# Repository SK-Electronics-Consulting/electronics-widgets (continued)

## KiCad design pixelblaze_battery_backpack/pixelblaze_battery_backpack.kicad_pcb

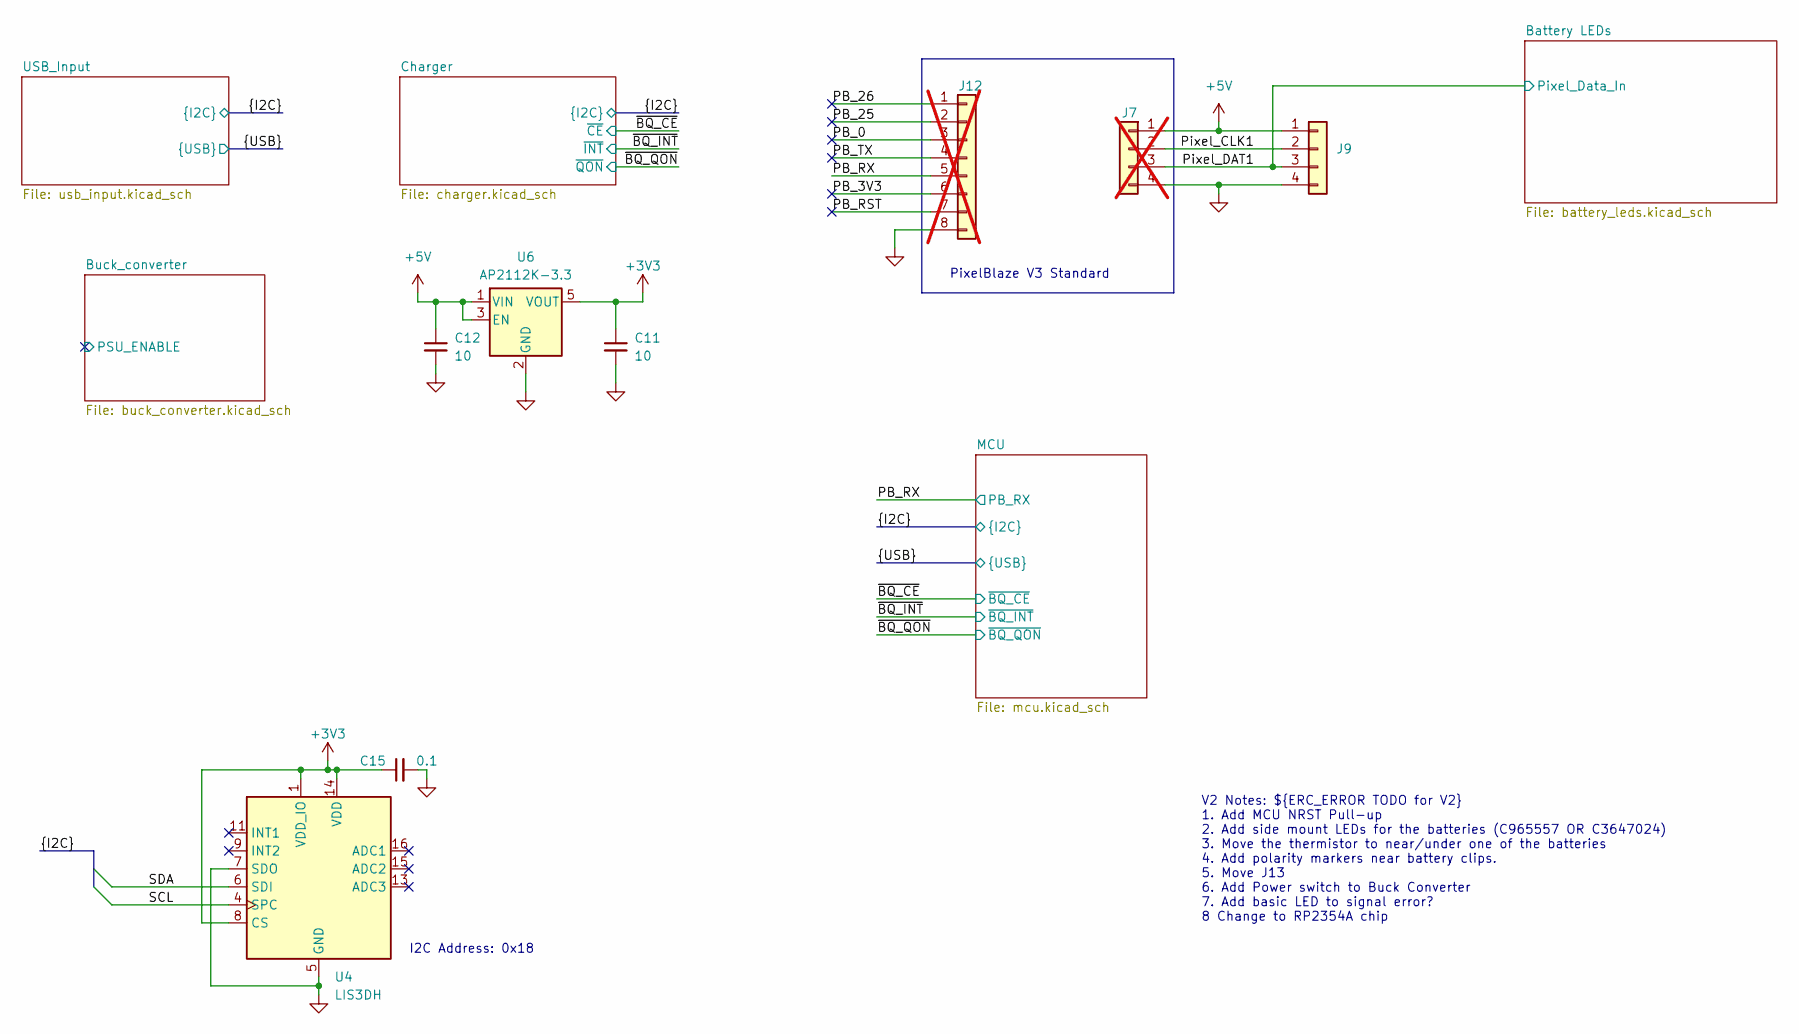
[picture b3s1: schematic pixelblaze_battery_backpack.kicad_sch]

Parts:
C11, C12: 10; C_0603_1608Metric; MPN GRM188R6YA106MA73D; JLCPCB Part No. C194427
C15: 0.1; C_0402_1005Metric; MPN GRM155R62A104KE14D; JLCPCB Part No. C162178
J7: Conn_01x04; PinHeader_1x04_P2.54mm_Vertical; not fitted
J9: Conn_01x04; Molex_Micro-Fit_3.0_43650-0415_1x04_P3.00mm_Vertical; MPN 436500415; JLCPCB Part No. C293547
J12: Conn_01x08; PinHeader_1x08_P2.54mm_Vertical; not fitted
U4: LIS3DH; LGA-16_3x3mm_P0.5mm_LayoutBorder3x5y; MPN LIS3DHTR; JLCPCB Part No. C15134
U6: AP2112K-3.3; SOT-23-5; MPN AP2112K-3.3TRG1; JLCPCB Part No. C51118

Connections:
+3V3: C11.1, C15.1, U4.1 (VDD_IO), U4.8 (CS), U4.14 (VDD), U6.5 (VOUT); also elsewhere on the board
+5V: C12.1, J7.1, J9.1, U6.1 (VIN), U6.3 (EN); also elsewhere on the board
/PB_0: J12.3
/PB_3V3: J12.6
/PB_25: J12.2
/PB_26: J12.1
/PB_RST: J12.7
/PB_RX: J12.5; also elsewhere on the board
/PB_TX: J12.4
/Pixel_CLK1: J7.2, J9.2
/Pixel_DAT1: J7.3, J9.3; also elsewhere on the board
/SCL: U4.4 (SPC); also elsewhere on the board
/SDA: U4.6 (SDI); also elsewhere on the board
GND: C11.2, C12.2, C15.2, J7.4, J9.4, J12.8, U4.5 (GND), U4.7 (SDO), U4.10 (GND), U4.12 (GND), U6.2 (GND); also elsewhere on the board

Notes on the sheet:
V2 Notes: ${ERC_ERROR TODO for V2} 1. Add MCU NRST Pull-up 2. Add side mount LEDs for the batteries (C965557 OR C3647024) 3. Move the thermistor to near/under one of the batteries 4. Add polarity markers near battery clips. 5. Move J13 6. Add Power switch to Buck Converter 7. Add basic LED to signa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
I2C Address: 0x18
PixelBlaze V3 Standard

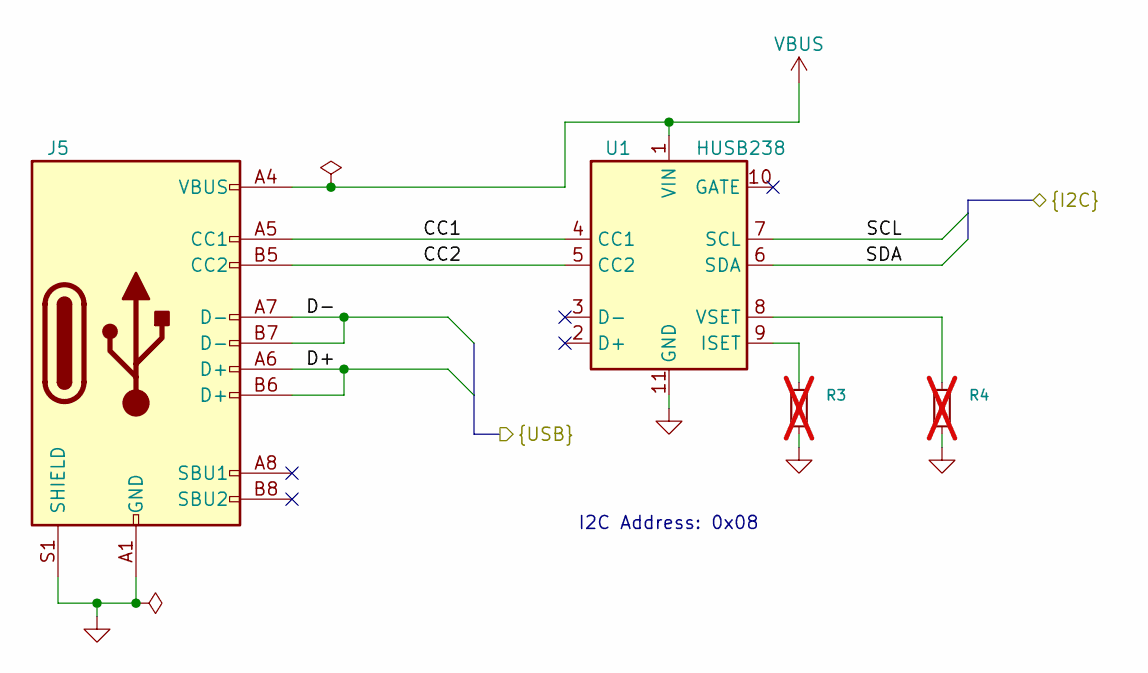
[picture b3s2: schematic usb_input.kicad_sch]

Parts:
J5: USB_C_Receptacle_USB2.0_16P; USB_C_Receptacle_HRO_TYPE-C-31-M-12; MPN TYPE-C-31-M-12; JLCPCB Part No. C165948
R3, R4: R_Small; R_0402_1005Metric; not fitted
U1: HUSB238; WDFN-10-1EP_3x3mm_P0.5mm_EP1.8x2.5mm; MPN HUSB238_002DD; JLCPCB Part No. C7471904

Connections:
/D+: J5.A6 (D+), J5.B6 (D+); also elsewhere on the board
/D-: J5.A7 (D-), J5.B7 (D-); also elsewhere on the board
/SCL: U1.7 (SCL); also elsewhere on the board
/SDA: U1.6 (SDA); also elsewhere on the board
/USB_Input/CC1: J5.A5 (CC1), U1.4 (CC1)
/USB_Input/CC2: J5.B5 (CC2), U1.5 (CC2)
GND: J5.A1 (GND), J5.A12 (GND), J5.B1 (GND), J5.B12 (GND), J5.S1 (SHIELD), J5.SH (SHIELD), R3.2, R4.2, U1.11 (GND); also elsewhere on the board
unnamed: R3.1, U1.9 (ISET)
unnamed: R4.1, U1.8 (VSET)
VBUS: J5.A4 (VBUS), J5.A9 (VBUS), J5.B4 (VBUS), J5.B9 (VBUS), U1.1 (VIN); also elsewhere on the board

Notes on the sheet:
I2C Address: 0x08

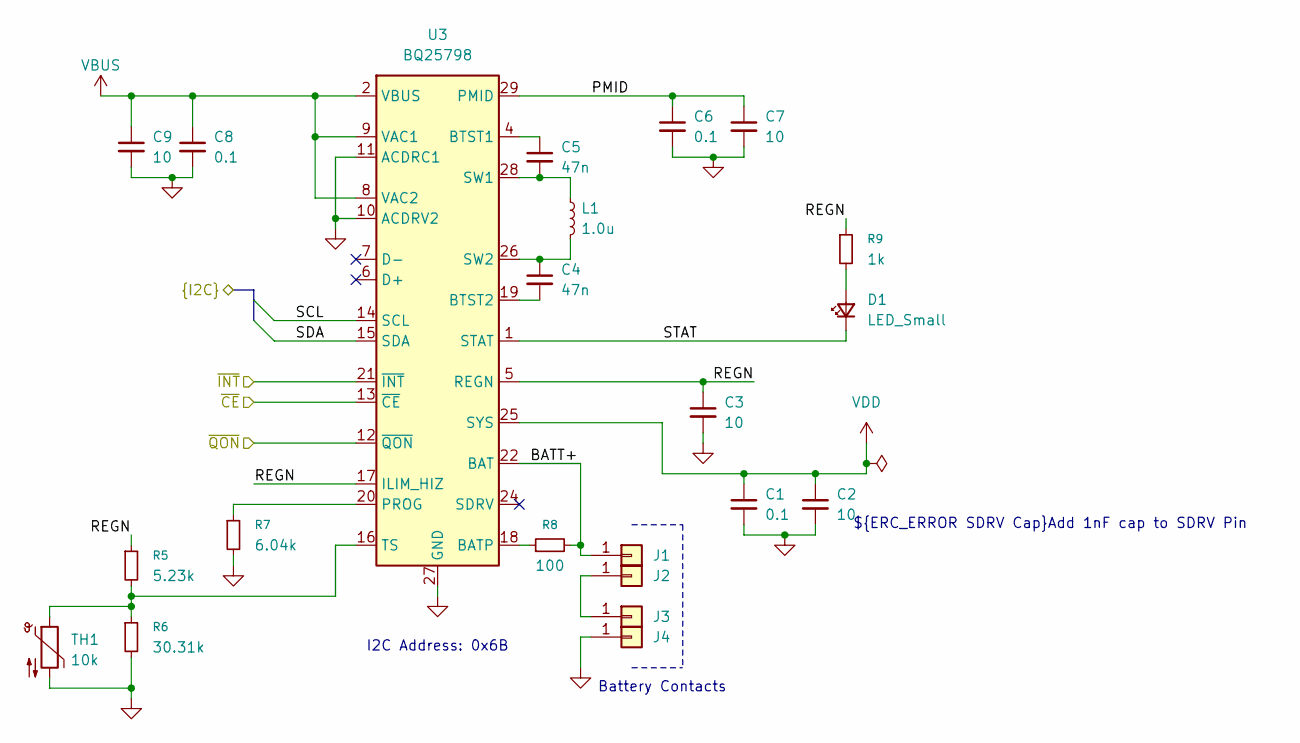
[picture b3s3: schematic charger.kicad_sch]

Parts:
C1, C6, C8: 0.1; C_0402_1005Metric; MPN GRM155R62A104KE14D; JLCPCB Part No. C162178
C2, C3, C7, C9: 10; C_0603_1608Metric; MPN GRM188R6YA106MA73D; JLCPCB Part No. C194427
C4, C5: 47n; C_0402_1005Metric; MPN CC0402KRX7R9BB473; JLCPCB Part No. C272875
D1: LED_Small; LED_0603_1608Metric; MPN XL-1608SURC-06; JLCPCB Part No. C965799
J1, J2, J3, J4: Conn_01x01; BatteryClip_MYoung_MY-18650-01; MPN MY-18650-01; JLCPCB Part No. C2979183
L1: 1.0u; L_Changjiang_FXL0630; MPN FXL0630-1R0-M; JLCPCB Part No. C167216
R5: 5.23k; R_0402_1005Metric; MPN FRC0402F5231TS; JLCPCB Part No. C2933105
R6: 30.31k; R_0402_1005Metric; MPN RC0402FR-0730K1L; JLCPCB Part No. C138009
R7: 6.04k; R_0402_1005Metric; MPN 0402WGF6041TCE; JLCPCB Part No. C25913
R8: 100; R_0402_1005Metric; MPN RC0402FR-07100RL; JLCPCB Part No. C106232
R9: 1k; R_0402_1005Metric; MPN RC0402FR-071KL; JLCPCB Part No. C106235
TH1: 10k; R_0603_1608Metric; MPN NCP18XH103F03RB; JLCPCB Part No. C13564
U3: BQ25798; Texas_RQM0029A_VQFN-29_4x4mm_P0.4mm; MPN BQ25798RQMR; JLCPCB Part No. C2876593

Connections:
/Charger/BATT+: J1.1, R8.2, U3.22 (BAT), U3.23 (BAT); also elsewhere on the board
/Charger/PMID: C6.1, C7.1, U3.29 (PMID)
/Charger/REGN: C3.1, R5.1, R9.1, U3.5 (REGN), U3.17 (ILIM_HIZ)
/Charger/STAT: D1.1 (K), U3.1 (STAT)
/SCL: U3.14 (SCL); also elsewhere on the board
/SDA: U3.15 (SDA); also elsewhere on the board
/~BQ_CE: U3.13 (~CE); also elsewhere on the board
/~BQ_INT: U3.21 (~INT); also elsewhere on the board
/~BQ_QON: U3.12 (~QON); also elsewhere on the board
GND: C1.2, C2.2, C3.2, C6.2, C7.2, C8.2, C9.2, J4.1, R6.2, R7.2, TH1.2, U3.10 (ACDRV2), U3.11 (ACDRV1), U3.27 (GND); also elsewhere on the board
unnamed: D1.2 (A), R9.2
unnamed: J2.1, J3.1
unnamed: R8.1, U3.18 (BATP)
unnamed: C5.1, U3.4 (BTST1)
unnamed: C4.2, U3.19 (BTST2)
unnamed: R7.1, U3.20 (PROG)
unnamed 75: U3.24 (SDRV); also elsewhere on the board
unnamed: C5.2, L1.1, U3.28 (SW1)
unnamed: C4.1, L1.2, U3.26 (SW2)
unnamed: R5.2, R6.1, TH1.1, U3.16 (TS)
VBUS: C8.1, C9.1, U3.2 (VBUS), U3.3 (VBUS), U3.8 (VAC2), U3.9 (VAC1); also elsewhere on the board
VDD: C1.1, C2.1, U3.25 (SYS); also elsewhere on the board

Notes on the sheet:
Battery Contacts
${ERC_ERROR SDRV Cap}Add 1nF cap to SDRV Pin
I2C Address: 0x6B

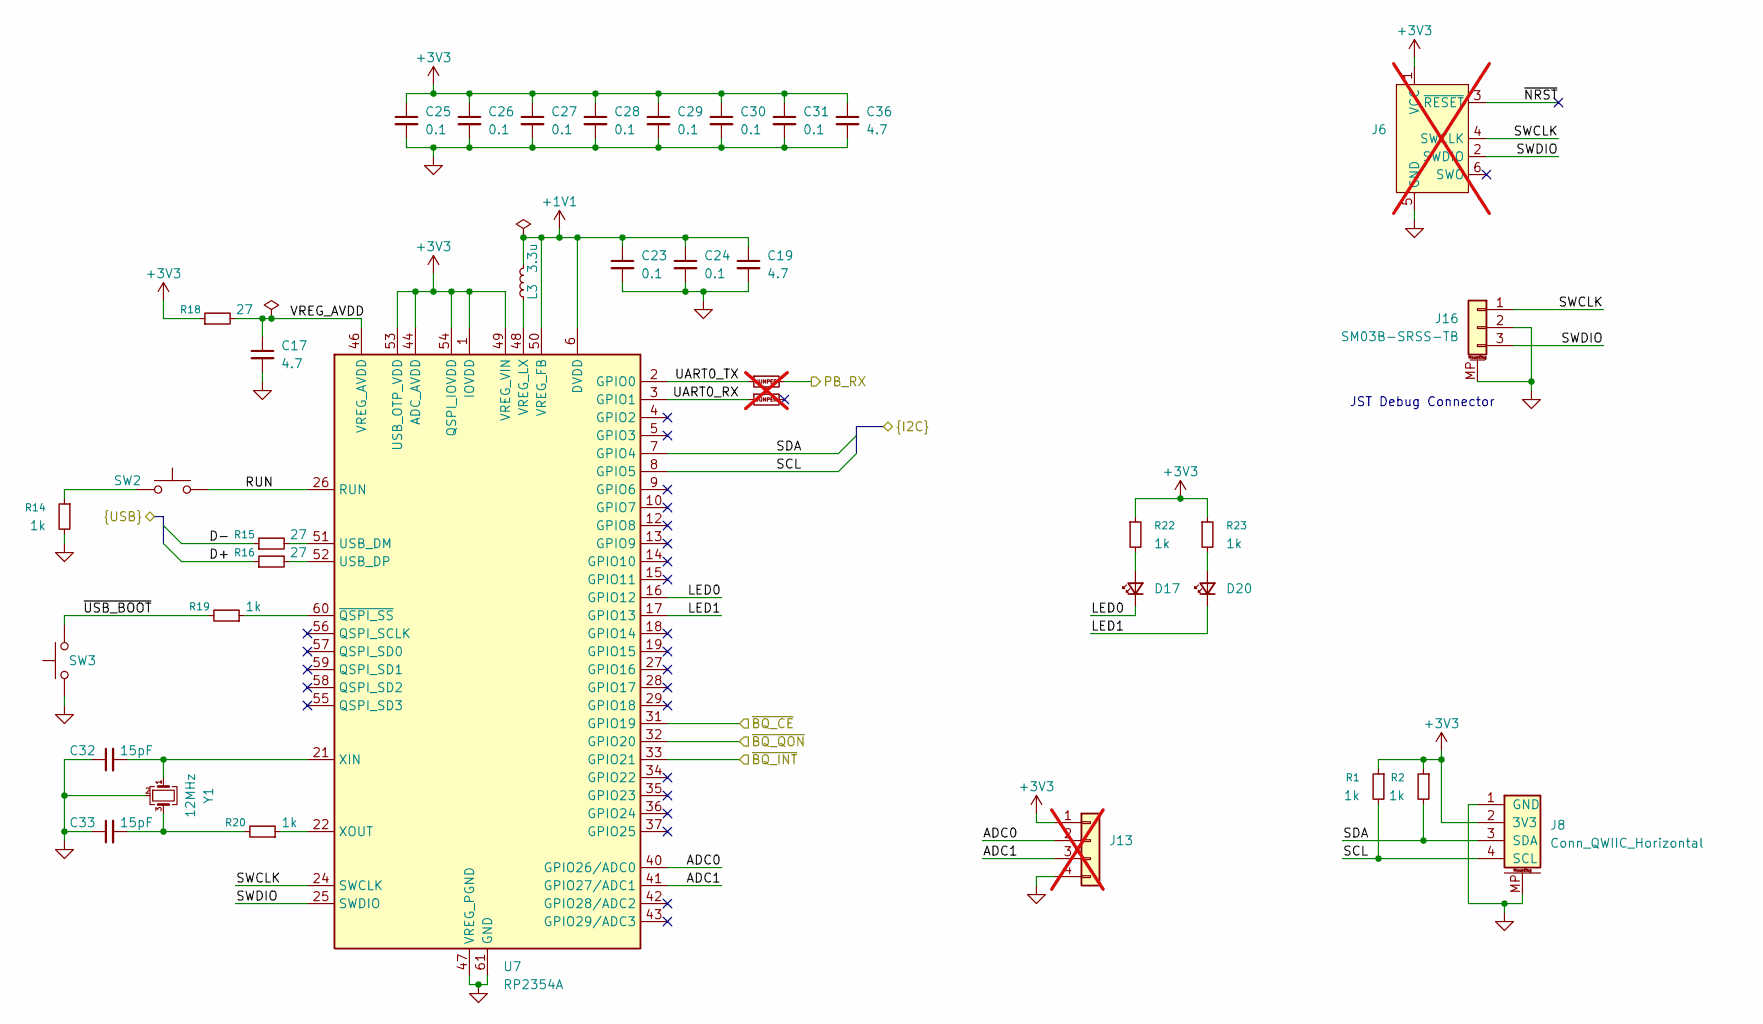
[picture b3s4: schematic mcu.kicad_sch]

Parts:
C17, C19, C36: 4.7; C_0402_1005Metric; MPN CGA0402X5R475M250GT; JLCPCB Part No. C6119795
C23, C24, C25, C26, C27, C28, C29, C30, C31: 0.1; C_0402_1005Metric; MPN GRM155R62A104KE14D; JLCPCB Part No. C162178
C32, C33: 15pF; C_0402_1005Metric; MPN CC0402JRNPO9BN150; JLCPCB Part No. C106997
D17, D20: LED_Small; LED_0603_1608Metric; MPN XL-1608SURC-06; JLCPCB Part No. C965799
J6: Conn_ARM_SWD_TagConnect_TC2030; Tag-Connect_TC2030-IDC-FP_2x03_P1.27mm_Vertical; not fitted
J8: Conn_QWIIC_Horizontal; JST_SH_SM04B-SRSS-TB_1x04-1MP_P1.00mm_Horizontal; MPN SM04B-SRSS-TB(LF)(SN); Digi-Key 455-SM04B-SRSS-TBCT-ND
J13: Conn_01x04; PinHeader_1x04_P2.54mm_Vertical; not fitted
J16: SM03B-SRSS-TB; JST_SH_SM03B-SRSS-TB_1x03-1MP_P1.00mm_Horizontal; JLCPCB Part No. C160403
L3: 3.3u; L_0806_2016Metric; MPN AOTA-B201610S3R3-101-T; JLCPCB Part No. C42411119
R1, R2, R14, R19, R20, R22, R23: 1k; R_0402_1005Metric; MPN RC0402FR-071KL; JLCPCB Part No. C106235
R15, R16, R18: 27; R_0402_1005Metric; MPN RC0402FR-0727RL; JLCPCB Part No. C138021
R21: RX_TX_Swap_SMD; RX_TX_SWAP_0402; not fitted
SW2, SW3: SW_Push; SW_SPST_TS-1088-xR020; MPN TS-1088-AR02016; JLCPCB Part No. C720477
U7: RP2354A; QFN-60-1EP_7x7mm_P0.4mm_EP3.4x3.4mm; MPN RP2354A; JLCPCB Part No. C41378174
Y1: 12MHz; Crystal_SMD_3225-4Pin_3.2x2.5mm; MPN ABM8-272-T3; JLCPCB Part No. C20625731

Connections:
+1V1: C19.1, C23.1, C24.1, L3.1, U7.6 (DVDD), U7.23 (DVDD), U7.39 (DVDD), U7.50 (VREG_FB)
+3V3: C25.1, C26.1, C27.1, C28.1, C29.1, C30.1, C31.1, C36.1, J6.1 (VCC), J8.2 (3V3), J13.1, R1.1, R2.1, R18.1, R22.1, R23.1, U7.1 (IOVDD), U7.11 (IOVDD), U7.20 (IOVDD), U7.30 (IOVDD), U7.38 (IOVDD), U7.44 (ADC_AVDD), U7.45 (IOVDD), U7.49 (VREG_VIN), U7.53 (USB_OTP_VDD), U7.54 (QSPI_IOVDD); also elsewhere on the board
/D+: R16.1; also elsewhere on the board
/D-: R15.1; also elsewhere on the board
/MCU/ADC0: J13.2, U7.40 (GPIO26/ADC0)
/MCU/ADC1: J13.3, U7.41 (GPIO27/ADC1)
/MCU/LED0: D17.1 (K), U7.16 (GPIO12)
/MCU/LED1: D20.1 (K), U7.17 (GPIO13)
/MCU/RUN: SW2.2, U7.26 (RUN)
/MCU/SWCLK: J6.4 (SWCLK), J16.1, U7.24 (SWCLK)
/MCU/SWDIO: J6.2 (SWDIO), J16.3, U7.25 (SWDIO)
/MCU/UART0_RX: R21.1B, U7.3 (GPIO1)
/MCU/UART0_TX: R21.1A, U7.2 (GPIO0)
/MCU/VREG_AVDD: C17.1, R18.2, U7.46 (VREG_AVDD)
/MCU/~NRST: J6.3 (~RESET)
/MCU/~USB_BOOT: R19.2, SW3.2
/PB_RX: R21.2A; also elsewhere on the board
/SCL: J8.4 (SCL), R1.2, U7.8 (GPIO5); also elsewhere on the board
/SDA: J8.3 (SDA), R2.2, U7.7 (GPIO4); also elsewhere on the board
/~BQ_CE: U7.31 (GPIO19); also elsewhere on the board
/~BQ_INT: U7.33 (GPIO21); also elsewhere on the board
/~BQ_QON: U7.32 (GPIO20); also elsewhere on the board
GND: C17.2, C19.2, C23.2, C24.2, C25.2, C26.2, C27.2, C28.2, C29.2, C30.2, C31.2, C32.1, C33.1, C36.2, J6.5 (GND), J8.1 (GND), J8.MP, J13.4, J16.2, J16.MP (MountPin), R14.2, SW3.1, U7.47 (VREG_PGND), U7.61 (GND), Y1.2 (G), Y1.4 (G); also elsewhere on the board
unnamed: C33.2, R20.2, Y1.3
unnamed: D17.2 (A), R22.2
unnamed: D20.2 (A), R23.2
unnamed: R14.1, SW2.1
unnamed: R15.2, U7.51 (USB_DM)
unnamed: R16.2, U7.52 (USB_DP)
unnamed: L3.2, U7.48 (VREG_LX)
unnamed: C32.2, U7.21 (XIN), Y1.1
unnamed: R20.1, U7.22 (XOUT)
unnamed: R19.1, U7.60 (~QSPI_SS)

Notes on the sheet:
JST Debug Connector

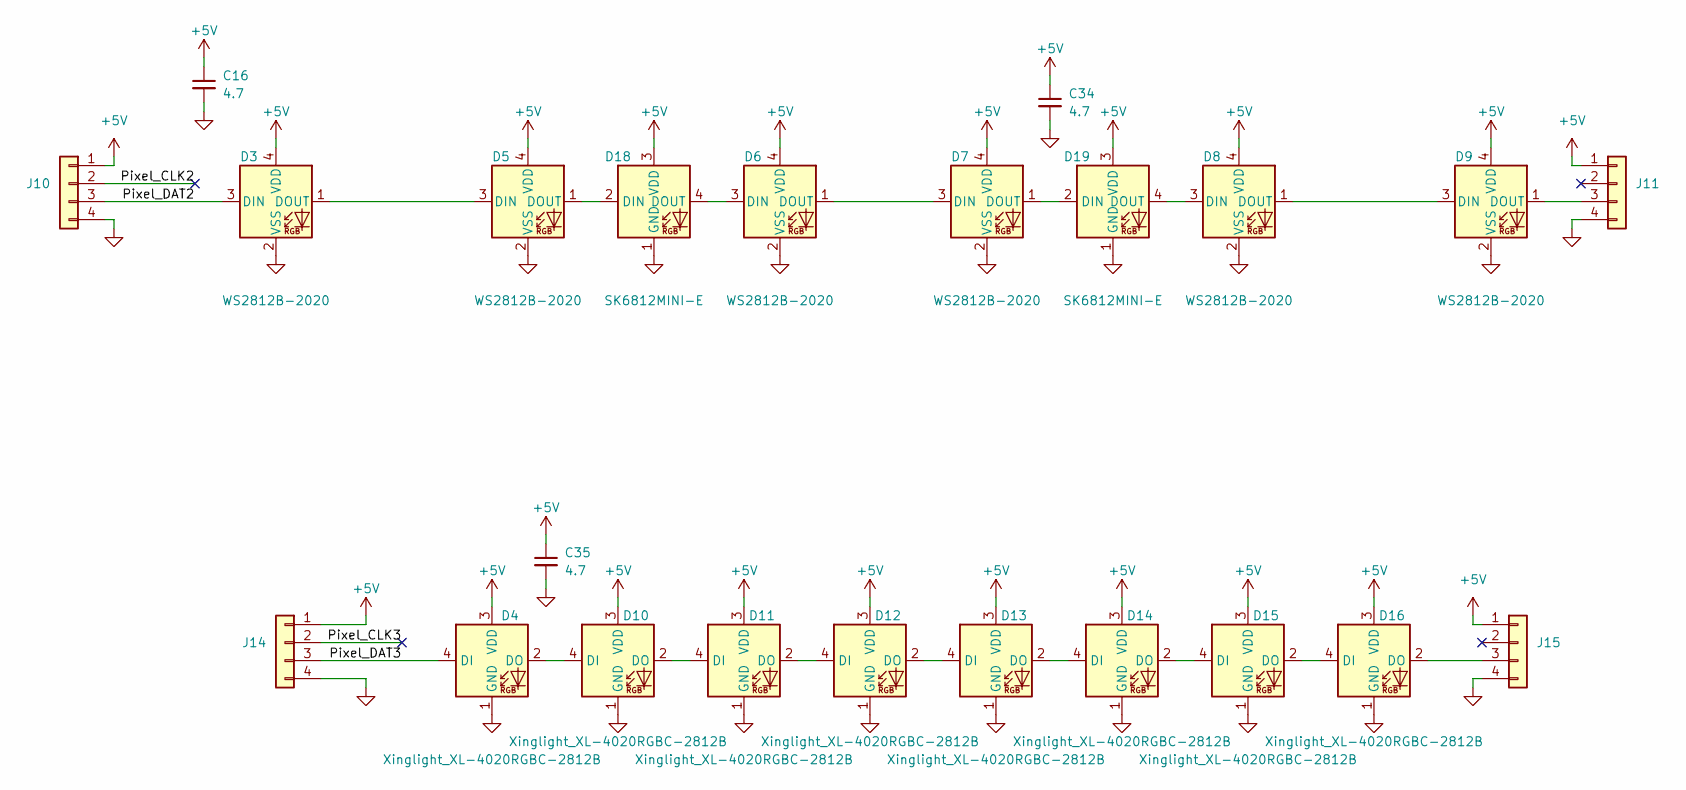
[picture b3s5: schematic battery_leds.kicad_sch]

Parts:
C16, C34, C35: 4.7; C_0402_1005Metric; MPN CGA0402X5R475M250GT; JLCPCB Part No. C6119795
D3, D5, D6, D7, D8, D9: WS2812B-2020; LED_WS2812B-2020_PLCC4_2.0x2.0mm; MPN XL-2020RGBC-2812B; JLCPCB Part No. C5349955
D4, D10, D11, D12, D13, D14, D15, D16: Xinglight_XL-4020RGBC-2812B; LED_Xinglight_XL-4020RGBC-2812B_4x2mm_P0.85mm
D18, D19: SK6812MINI-E; LED_SK6812MINI-E_3.2x2.8mm_P1.5mm_ReverseMount
J10, J11, J14, J15: Conn_01x04; Molex_Micro-Fit_3.0_43650-0415_1x04_P3.00mm_Vertical; MPN 436500415; JLCPCB Part No. C293547

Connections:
+5V: C16.1, C34.1, C35.1, D3.4 (VDD), D4.3 (VDD), D5.4 (VDD), D6.4 (VDD), D7.4 (VDD), D8.4 (VDD), D9.4 (VDD), D10.3 (VDD), D11.3 (VDD), D12.3 (VDD), D13.3 (VDD), D14.3 (VDD), D15.3 (VDD), D16.3 (VDD), D18.3 (VDD), D19.3 (VDD), J10.1, J11.1, J14.1, J15.1; also elsewhere on the board
/Battery LEDs/Pixel_CLK2: J10.2
/Battery LEDs/Pixel_CLK3: J14.2
/Battery LEDs/Pixel_DAT2: D3.3 (DIN), J10.3; also elsewhere on the board
/Battery LEDs/Pixel_DAT3: D4.4 (DI), J14.3; also elsewhere on the board
GND: C16.2, C34.2, C35.2, D3.2 (VSS), D4.1 (GND), D5.2 (VSS), D6.2 (VSS), D7.2 (VSS), D8.2 (VSS), D9.2 (VSS), D10.1 (GND), D11.1 (GND), D12.1 (GND), D13.1 (GND), D14.1 (GND), D15.1 (GND), D16.1 (GND), D18.1 (VSS), D19.1 (VSS), J10.4, J11.4, J14.4, J15.4; also elsewhere on the board
unnamed: D3.1 (DOUT), D5.3 (DIN)
unnamed: D6.1 (DOUT), D7.3 (DIN)
unnamed: D8.1 (DOUT), D9.3 (DIN)
unnamed 51: D9.1 (DOUT), J11.3; also elsewhere on the board
unnamed: D4.2 (DO), D10.4 (DI)
unnamed: D10.2 (DO), D11.4 (DI)
unnamed: D11.2 (DO), D12.4 (DI)
unnamed: D12.2 (DO), D13.4 (DI)
unnamed: D13.2 (DO), D14.4 (DI)
unnamed: D14.2 (DO), D15.4 (DI)
unnamed: D15.2 (DO), D16.4 (DI)
unnamed: D16.2 (DO), J15.3
unnamed: D5.1 (DOUT), D18.2 (DIN)
unnamed: D6.3 (DIN), D18.4 (DOUT)
unnamed: D7.1 (DOUT), D19.2 (DIN)
unnamed: D8.3 (DIN), D19.4 (DOUT)

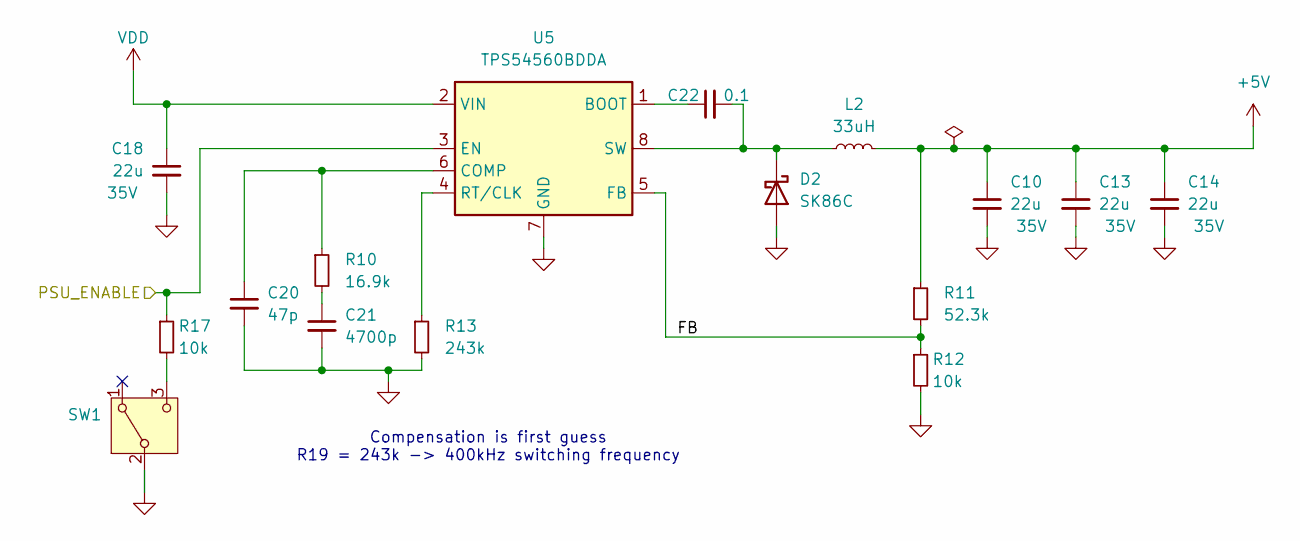
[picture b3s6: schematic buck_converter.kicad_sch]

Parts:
C10, C13, C14, C18: 22u; C_0805_2012Metric; Voltage 35V; MPN CGA0805X5R226M350MT; JLCPCB Part No. C6119901
C20: 47p; C_0402_1005Metric; Voltage 50V; MPN 0402CG470J500NT; JLCPCB Part No. C1567
C21: 4700p; C_0402_1005Metric; Voltage 50V; MPN GRM1555C1H472JE01D; JLCPCB Part No. C1518204
C22: 0.1; C_0402_1005Metric; MPN GRM155R62A104KE14D; JLCPCB Part No. C162178
D2: SK86C; D_SMC; MPN SK86C; JLCPCB Part No. C64338
L2: 33uH; L_Changjiang_FXL1040; MPN FXL1040-330-M; JLCPCB Part No. C475918
R10: 16.9k; R_0402_1005Metric; MPN RC0402FR-0716K9L; JLCPCB Part No. C163488
R11: 52.3k; R_0402_1005Metric; MPN 0402WGF5232TCE; JLCPCB Part No. C26982
R12, R17: 10k; R_0402_1005Metric; MPN RC0402FR-0710KL; JLCPCB Part No. C60490
R13: 243k; R_0402_1005Metric; MPN RC0402FR-07243KL; JLCPCB Part No. C138028
SW1: SW_SPDT; SW_SPDT_Shouhan_MSK12C02; MPN MSK12C02; JLCPCB Part No. C431540
U5: TPS54560BDDA; Texas_R-PDSO-G8_EP2.95x4.9mm_Mask2.4x3.1mm_ThermalVias; MPN TPS54560BDDAR; JLCPCB Part No. C1850354

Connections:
+5V: C10.1, C13.1, C14.1, L2.2, R11.1; also elsewhere on the board
/Buck_converter/FB: R11.2, R12.1, U5.5 (FB)
/Buck_converter/PSU_ENABLE: R17.1, U5.3 (EN)
GND: C10.2, C13.2, C14.2, C18.2, C20.2, C21.2, D2.2 (A), R12.2, R13.2, SW1.2 (B), U5.7 (GND), U5.9 (GND); also elsewhere on the board
unnamed: C21.1, R10.2
unnamed: C22.2, D2.1 (K), L2.1, U5.8 (SW)
unnamed: R17.2, SW1.3 (C)
unnamed: C22.1, U5.1 (BOOT)
unnamed: C20.1, R10.1, U5.6 (COMP)
unnamed: R13.1, U5.4 (RT/CLK)
VDD: C18.1, U5.2 (VIN); also elsewhere on the board

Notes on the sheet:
Compensation is first guess R19 = 243k -> 400kHz switching frequency

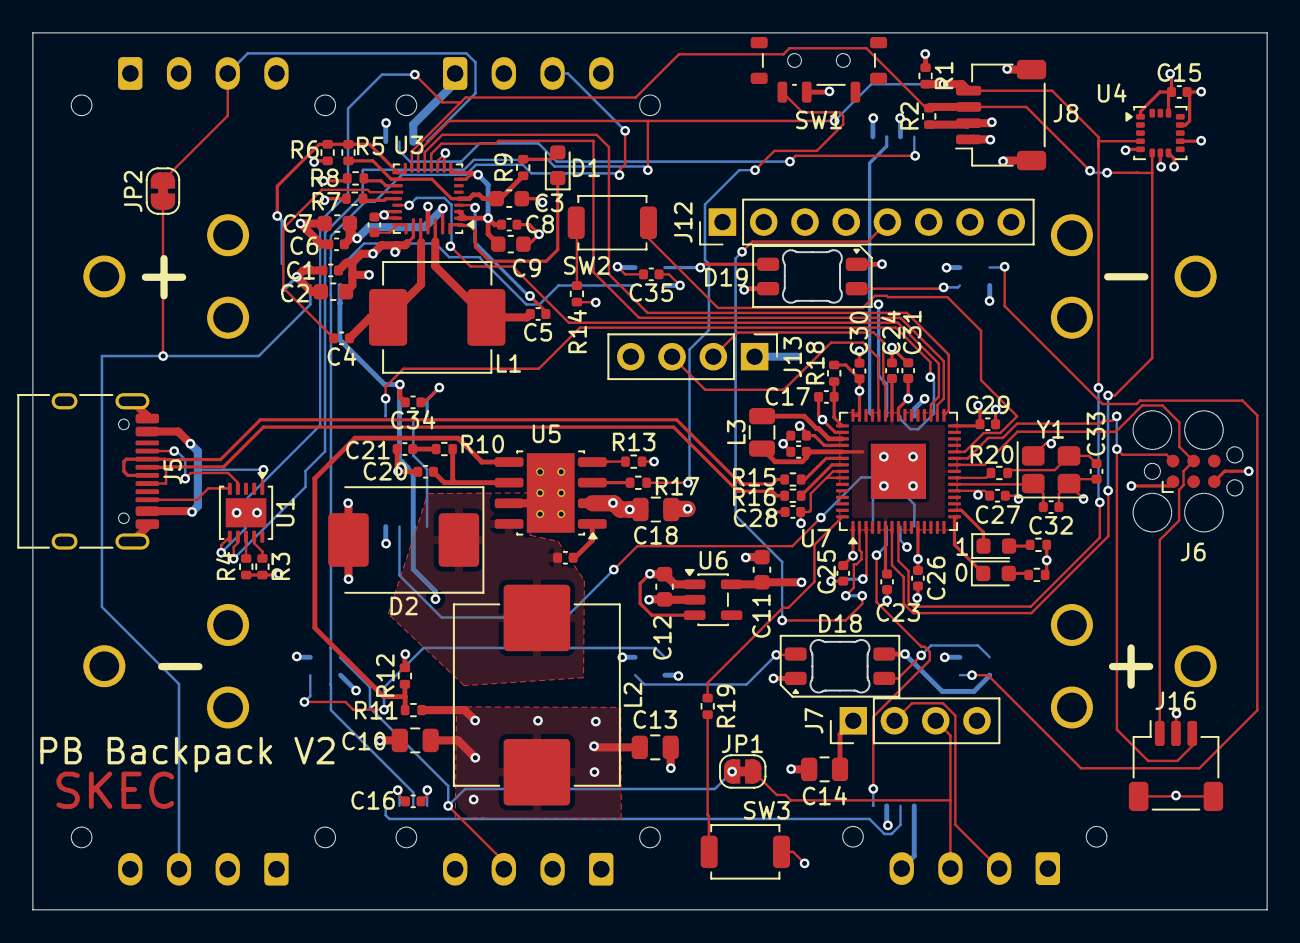
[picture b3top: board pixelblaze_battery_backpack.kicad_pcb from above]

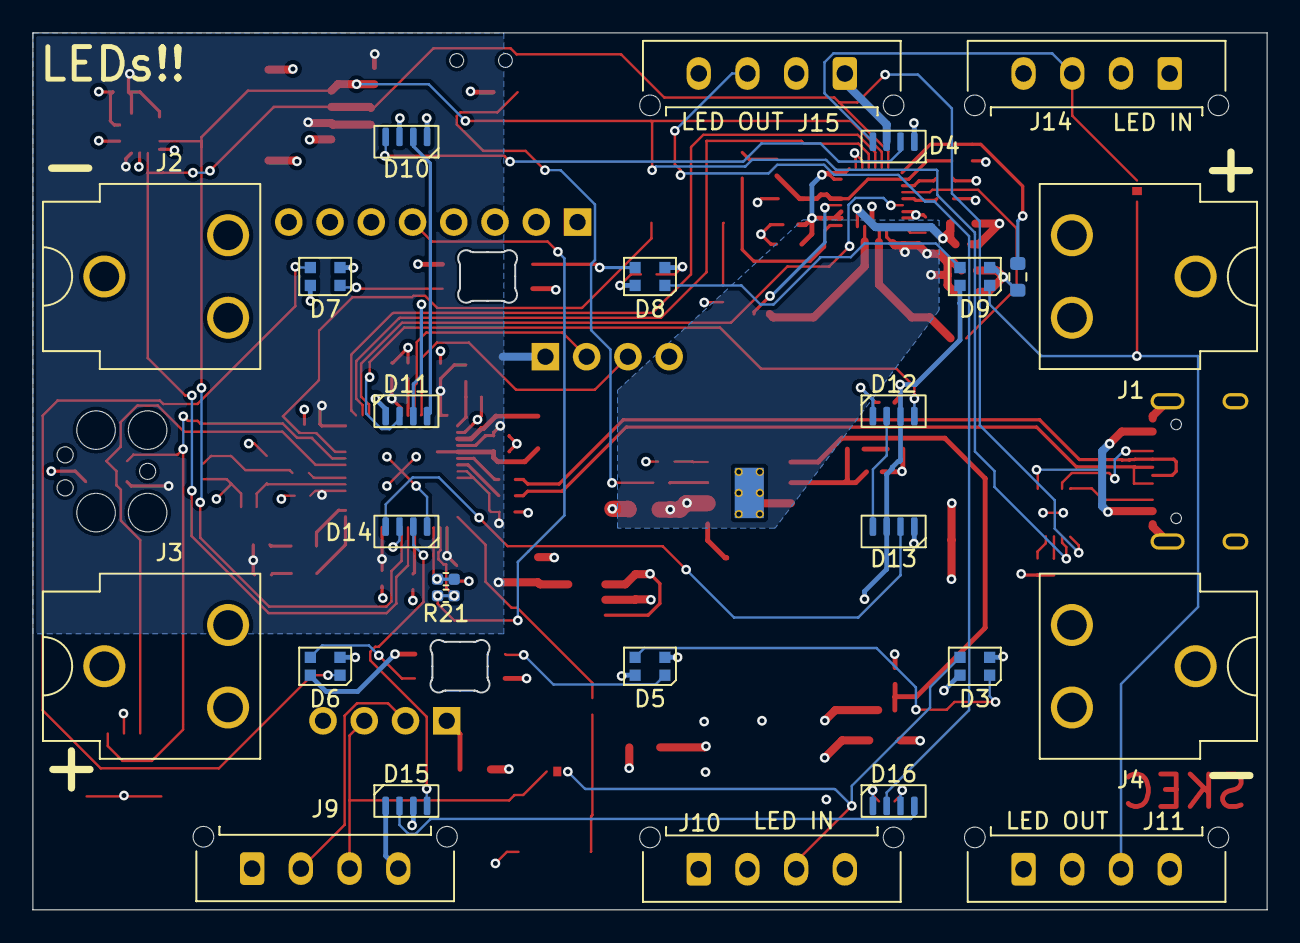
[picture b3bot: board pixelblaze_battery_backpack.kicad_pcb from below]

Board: 4 copper layers, 75.9 x 53.9 mm, 112 parts (25 on the bottom side), 81 nets.

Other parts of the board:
C37: 1n; C_0402_1005Metric
JP1, JP2: Jumper_2_Small_Bridged; SolderJumper-2_P1.3mm_Bridged_RoundedPad1.0x1.5mm

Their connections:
/Battery LEDs/Pixel_DAT2: JP1.2 (B); also elsewhere on the board
/Battery LEDs/Pixel_DAT3: JP2.2 (B); also elsewhere on the board
/Charger/BATT+: C37.1; also elsewhere on the board
/Pixel_DAT1: JP1.1 (A); also elsewhere on the board
unnamed 51: JP2.1 (A); also elsewhere on the board
unnamed 75: C37.2; also elsewhere on the board

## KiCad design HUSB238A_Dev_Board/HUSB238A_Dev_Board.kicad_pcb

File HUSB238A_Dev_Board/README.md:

# HUSB238A Dev Board

## TODO

* Add pull down from EN pin to GND
* Add Pull down from FET Gate to gnd. This is to bootstrap the power enable.

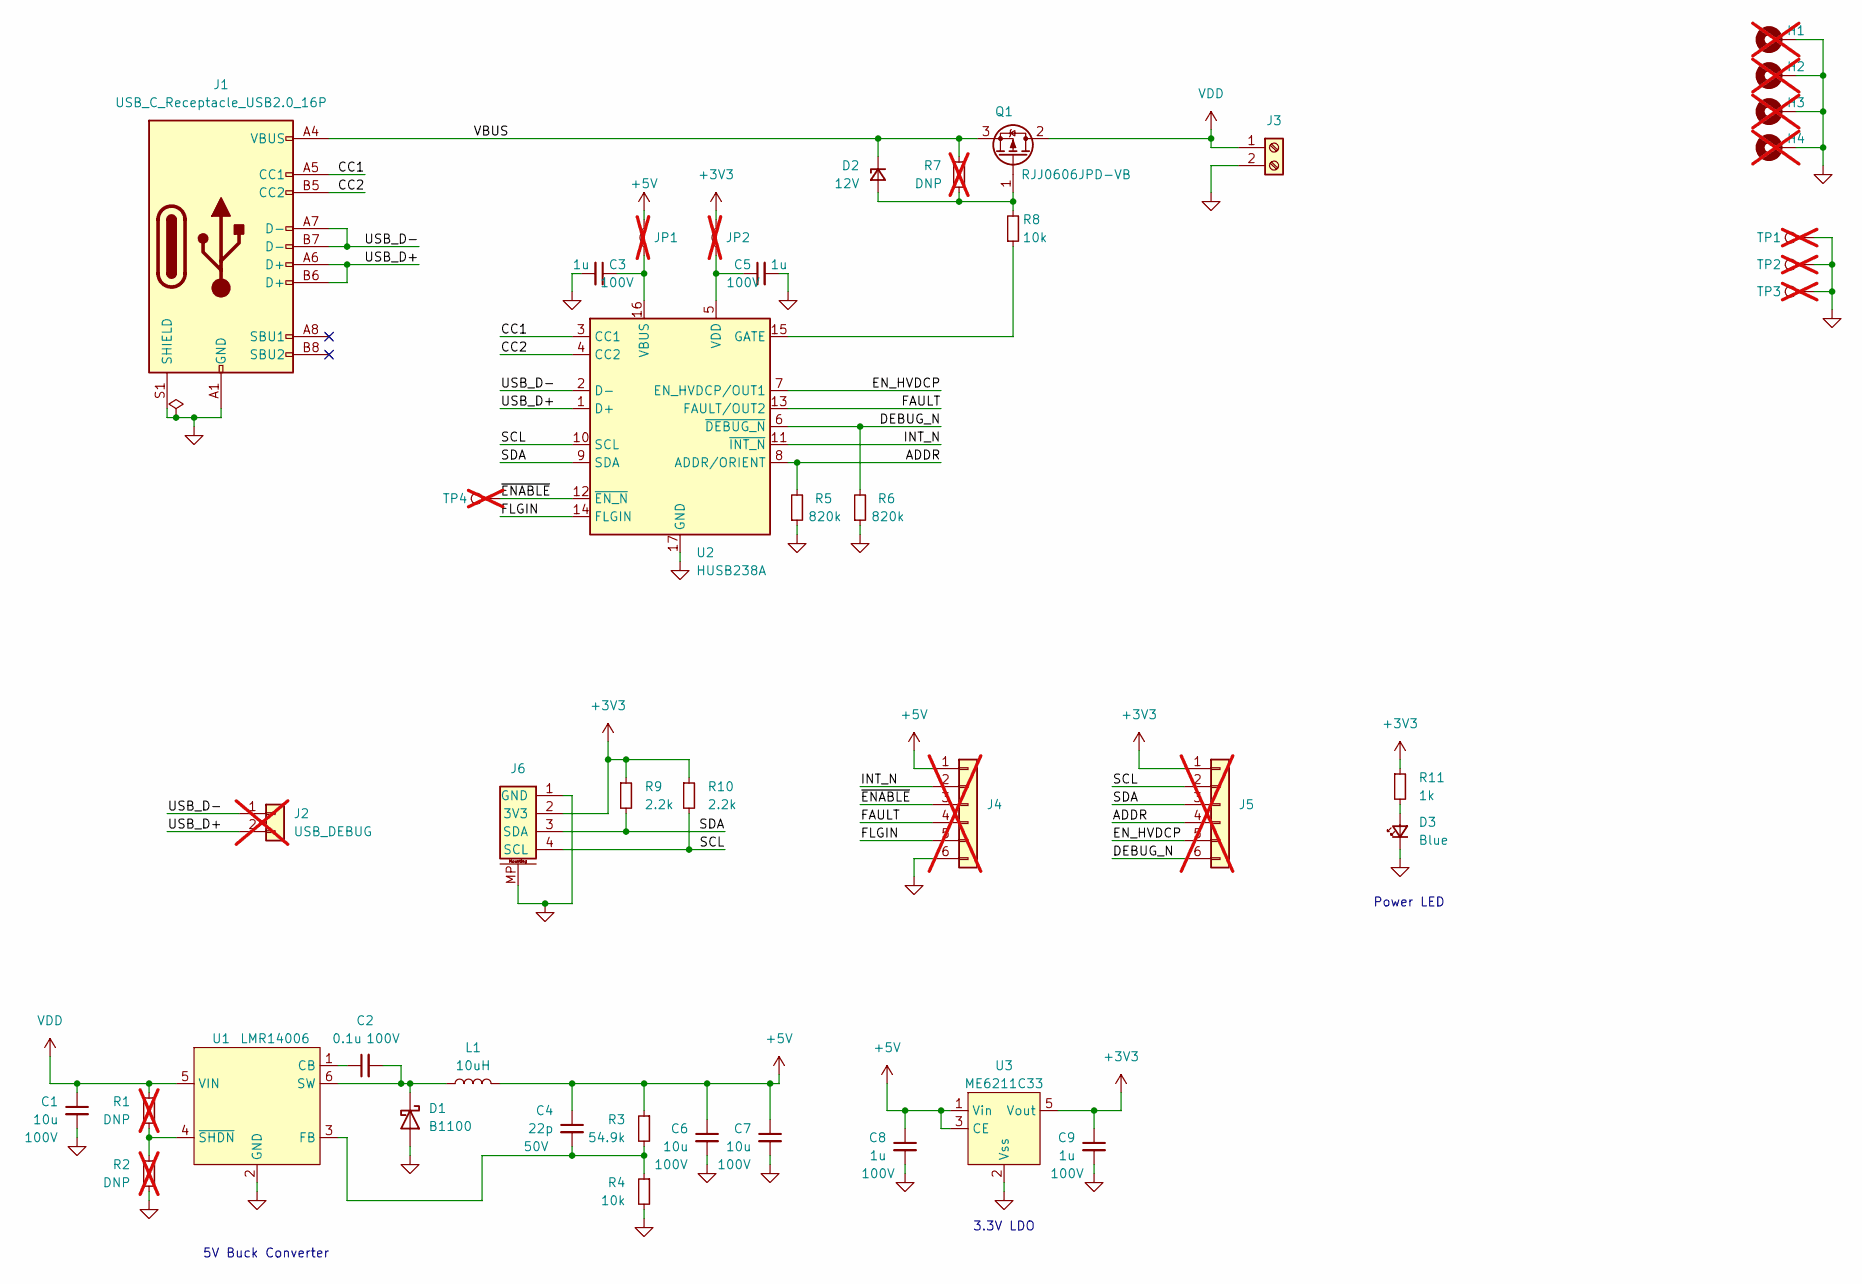
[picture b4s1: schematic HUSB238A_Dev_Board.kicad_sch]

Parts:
C1, C6, C7: 10u; C_1210_3225Metric; Voltage 100V; MPN C5156756
C2: 0.1u; C_0603_1608Metric; Voltage 100V; MPN C113803
C3, C5, C8, C9: 1u; C_0805_2012Metric; Voltage 100V; MPN C385977
C4: 22p; C_0402_1005Metric; Voltage 50V; MPN C883567
D1: B1100; D_SMA; MPN C110106
D2: 12V; D_SOD-123; Voltage 12V; MPN C173429
D3: Blue; LED_0603_1608Metric; MPN C7496819
H1, H2, H3, H4: MountingHole_Pad; MountingHole_3.2mm_M3_Pad_Via; not fitted
J1: USB_C_Receptacle_USB2.0_16P; USB_C_Receptacle_HRO_TYPE-C-31-M-12; MPN C165948
J2: USB_DEBUG; PinHeader_1x02_P2.54mm_Vertical; not fitted
J3: Screw_Terminal_01x02; TerminalBlock_Phoenix_MKDS-1,5-2_1x02_P5.00mm_Horizontal; MPN C8269
J4, J5: Conn_01x06; PinHeader_1x06_P2.54mm_Vertical; not fitted
J6: Conn_QWIIC_Horizontal; JST_SH_SM04B-SRSS-TB_1x04-1MP_P1.00mm_Horizontal; MPN C160404; Digi-Key 455-SM04B-SRSS-TBCT-ND
JP1: Jumper_2_Bridged; SolderJumper-2_P1.3mm_Bridged_Pad1.0x1.5mm; not fitted
JP2: SolderJumper-2_P1.3mm_Bridged_Pad1.0x1.5mm; not fitted
L1: 10uH; L_KOHERelec_MDA7030; MPN C2847543
Q1: RJJ0606JPD-VB; TO-252-2; MPN C18212486
R1, R2, R7: DNP; R_0402_1005Metric; not fitted
R3: 54.9k; R_0402_1005Metric; MPN C5126159
R4, R8: 10k; R_0402_1005Metric; MPN C60490
R5, R6: 820k; R_0402_1005Metric; MPN C273727
R9, R10: 2.2k; R_0402_1005Metric_Pad0.72x0.64mm_HandSolder
R11: 1k; R_0402_1005Metric; MPN C11702
TP1, TP2, TP4: TestPoint; TestPoint_THTPad_D1.0mm_Drill0.5mm; not fitted
TP3: TestPoint; TestPoint_Keystone_5010-5014_Multipurpose; not fitted
U1: LMR14006; SOT-23-6; MPN C477919
U2: HUSB238A; QFN-16-1EP_3x3mm_P0.5mm_EP1.7x1.7mm; MPN C24833806
U3: ME6211C33; SOT-23-5; MPN C82942

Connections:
+3V3: C9.1, J5.1, J6.2 (3V3), JP2.2 (B), R9.1, R10.1, R11.1, U3.5 (Vout)
+5V: C4.1, C6.1, C7.1, C8.1, J4.1, JP1.2 (B), L1.2, R3.1, U3.1 (Vin), U3.3 (CE)
/ADDR: J5.4, R5.2, U2.8 (ADDR/ORIENT)
/CC1: J1.A5 (CC1), U2.3 (CC1)
/CC2: J1.B5 (CC2), U2.4 (CC2)
/DEBUG_N: J5.6, R6.2, U2.6 (~DEBUG_N)
/EN_HVDCP: J5.5, U2.7 (EN_HVDCP/OUT1)
/FAULT: J4.4, U2.13 (FAULT/OUT2)
/FLGIN: J4.5, U2.14 (FLGIN)
/INT_N: J4.2, U2.11 (~INT_N)
/SCL: J5.2, J6.4 (SCL), R10.2, U2.10 (SCL)
/SDA: J5.3, J6.3 (SDA), R9.2, U2.9 (SDA)
/USB_D+: J1.A6 (D+), J1.B6 (D+), J2.2, U2.1 (D+)
/USB_D-: J1.A7 (D-), J1.B7 (D-), J2.1, U2.2 (D-)
/VBUS: D2.1 (K), J1.A4 (VBUS), J1.A9 (VBUS), J1.B4 (VBUS), J1.B9 (VBUS), Q1.3 (S), R7.2
/~ENABLE: J4.3, TP4.1, U2.12 (~EN_N)
GND: C1.2, C3.2, C5.2, C6.2, C7.2, C8.2, C9.2, D1.2 (A), D3.1 (K), H1.1, H2.1, H3.1, H4.1, J1.A1 (GND), J1.A12 (GND), J1.B1 (GND), J1.B12 (GND), J1.S1 (SHIELD), J3.2, J4.6, J6.1 (GND), J6.MP, R2.2, R4.2, R5.1, R6.1, TP1.1, TP2.1, TP3.1, U1.2 (GND), U2.17 (GND), U3.2 (Vss)
unnamed: C2.2, D1.1 (K), L1.1, U1.6 (SW)
unnamed: D2.2 (A), Q1.1 (G), R7.1, R8.2
unnamed: D3.2 (A), R11.2
unnamed: C3.1, JP1.1 (A), U2.16 (VBUS)
unnamed: C5.1, JP2.1 (A), U2.5 (VDD)
unnamed: C2.1, U1.1 (CB)
unnamed: C4.2, R3.2, R4.1, U1.3 (FB)
unnamed: R1.2, R2.1, U1.4 (~SHDN)
unnamed: R8.1, U2.15 (GATE)
VDD: C1.1, J3.1, Q1.2 (D), R1.1, U1.5 (VIN)

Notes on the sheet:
5V Buck Converter
3.3V LDO
Power LED
